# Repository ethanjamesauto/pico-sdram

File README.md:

# pico-sdram

This project attempts to interface a Raspberry Pi Pico with a [32MB SDRAM IC](https://www.winbond.com/resource-files/w9825g6kh_a04.pdf).

## UPDATE - Current State
I have been able to successfully perform single and burst read/writes to the W9825G6KH SDRAM IC. I am running the SDRAM at half the speed of the rp2040 clock - the PIO state machines
are running at the minimum clock divider value.
I don't have full documentation, but some is available in:
* [pico/src/sdram_cmd.c](pico/src/sdram_cmd.c) - contains the main driver code
* [pico/src/pico-sdram.c](pico/src/pico-sdram.c) - example usage of the driver code
* [pico/src/three_74hc595.pio](pico/src/three_74hc595.pio) - PIO driver for the 3x 74hc595 shift registers used to drive the address bus
* [pico/src/data_bus.pio](pico/src/data_bus.pio) - PIO driver for the 16-bit data bus

## Introduction
SDRAM ICs are commonly available in sizes of up to 256MBit (32MB), and most have either an 8-bit or 16-bit data bus width. The control interface uses a total of 23 pins, so there are simply too many pins for an RP2040 to directly drive using GPIOs. 

Shift registers may be reduce the number of GPIOs needed to interface with the ram. Because the RP2040 can only drive shift registers so quickly, the SDRAM chip would need to be driven at a lower clock speed. I propose a solution in which the control pins are driven using shift registers while the data bus is connected directly to the RP2040's GPIOs. This reduces the speed at which commands can be sent to the SDRAM, while still allowing the data bus to run at full speed. This solution has a drawback - it takes more time to send the two commands needed to initiate a read (row activate and read). However, this issue becomes neglible when most reads and writes use large block sizes (for example, when performing 1KB block reads and writes).

## Future Work
Eventually, I'd like to use this SDRAM interface with a PIO-based QSPI interface. The QSPI interface may then appear as a QSPI PSRAM and can be connected to the rp2350's QSPI bus. The pico can then translate "psram" accesses to sdram accesses, which would **allow the pico to natively access sdram in the address space**. This might not be possible.

## Digilent Waveforms SDRAM Protocol Decoder
```js
// rgData: input, raw digital data array
// rgValue: output, decoded data array
// rgFlag: output, decoded flag array

c = rgData.length

for(var i = 0; i < c; i++){
   // take 4 least significant bits
   rgValue[i] = rgData[i] & 0xFF;
   // set flag other than zero for valid data
   rgFlag[i] = 1;
}

// value: value sample
// flag: flag sample
function Value2Text(flag, value) {
  var lower = value & 0xf;
  var addr10 = ((value >> 7) & 1) > 0;
  if (lower & 1) return "";
  if (lower == 14) return "NOP";
  if (lower == 6) return "BURST_TERM";
  if (lower == 10) return addr10 ? "READ_PRECHARGE" : "READ";
  if (lower == 2) return addr10 ? "WRITE_PRECHARGE" : "WRITE";
  if (lower == 12) return "ACTIVATE";
  if (lower == 4) return "PRECHARGE";
  if (lower == 8) return "AUTO_REFRESH";
  if (lower == 0) return "LOAD_MODE";
  return "X";
}
Value2Text(0,0x82)

function Value2Text(flag, value) {
  var lower = value & 0xf;
  var addr10 = ((value >> 7) & 1) > 0;
  if (lower & 1) return "";
  if (lower == 14) return "NOP";
  if (lower == 6) return "BURST_T";
  if (lower == 10) return addr10 ? "READ_P" : "READ";
  if (lower == 2) return addr10 ? "WRITE_P" : "WRITE";
  if (lower == 12) return "ACTIVATE";
  if (lower == 4) return "PRCHG";
  if (lower == 8) return "A_RFRSH";
  if (lower == 0) return "MODE";
  return "X";
}
```

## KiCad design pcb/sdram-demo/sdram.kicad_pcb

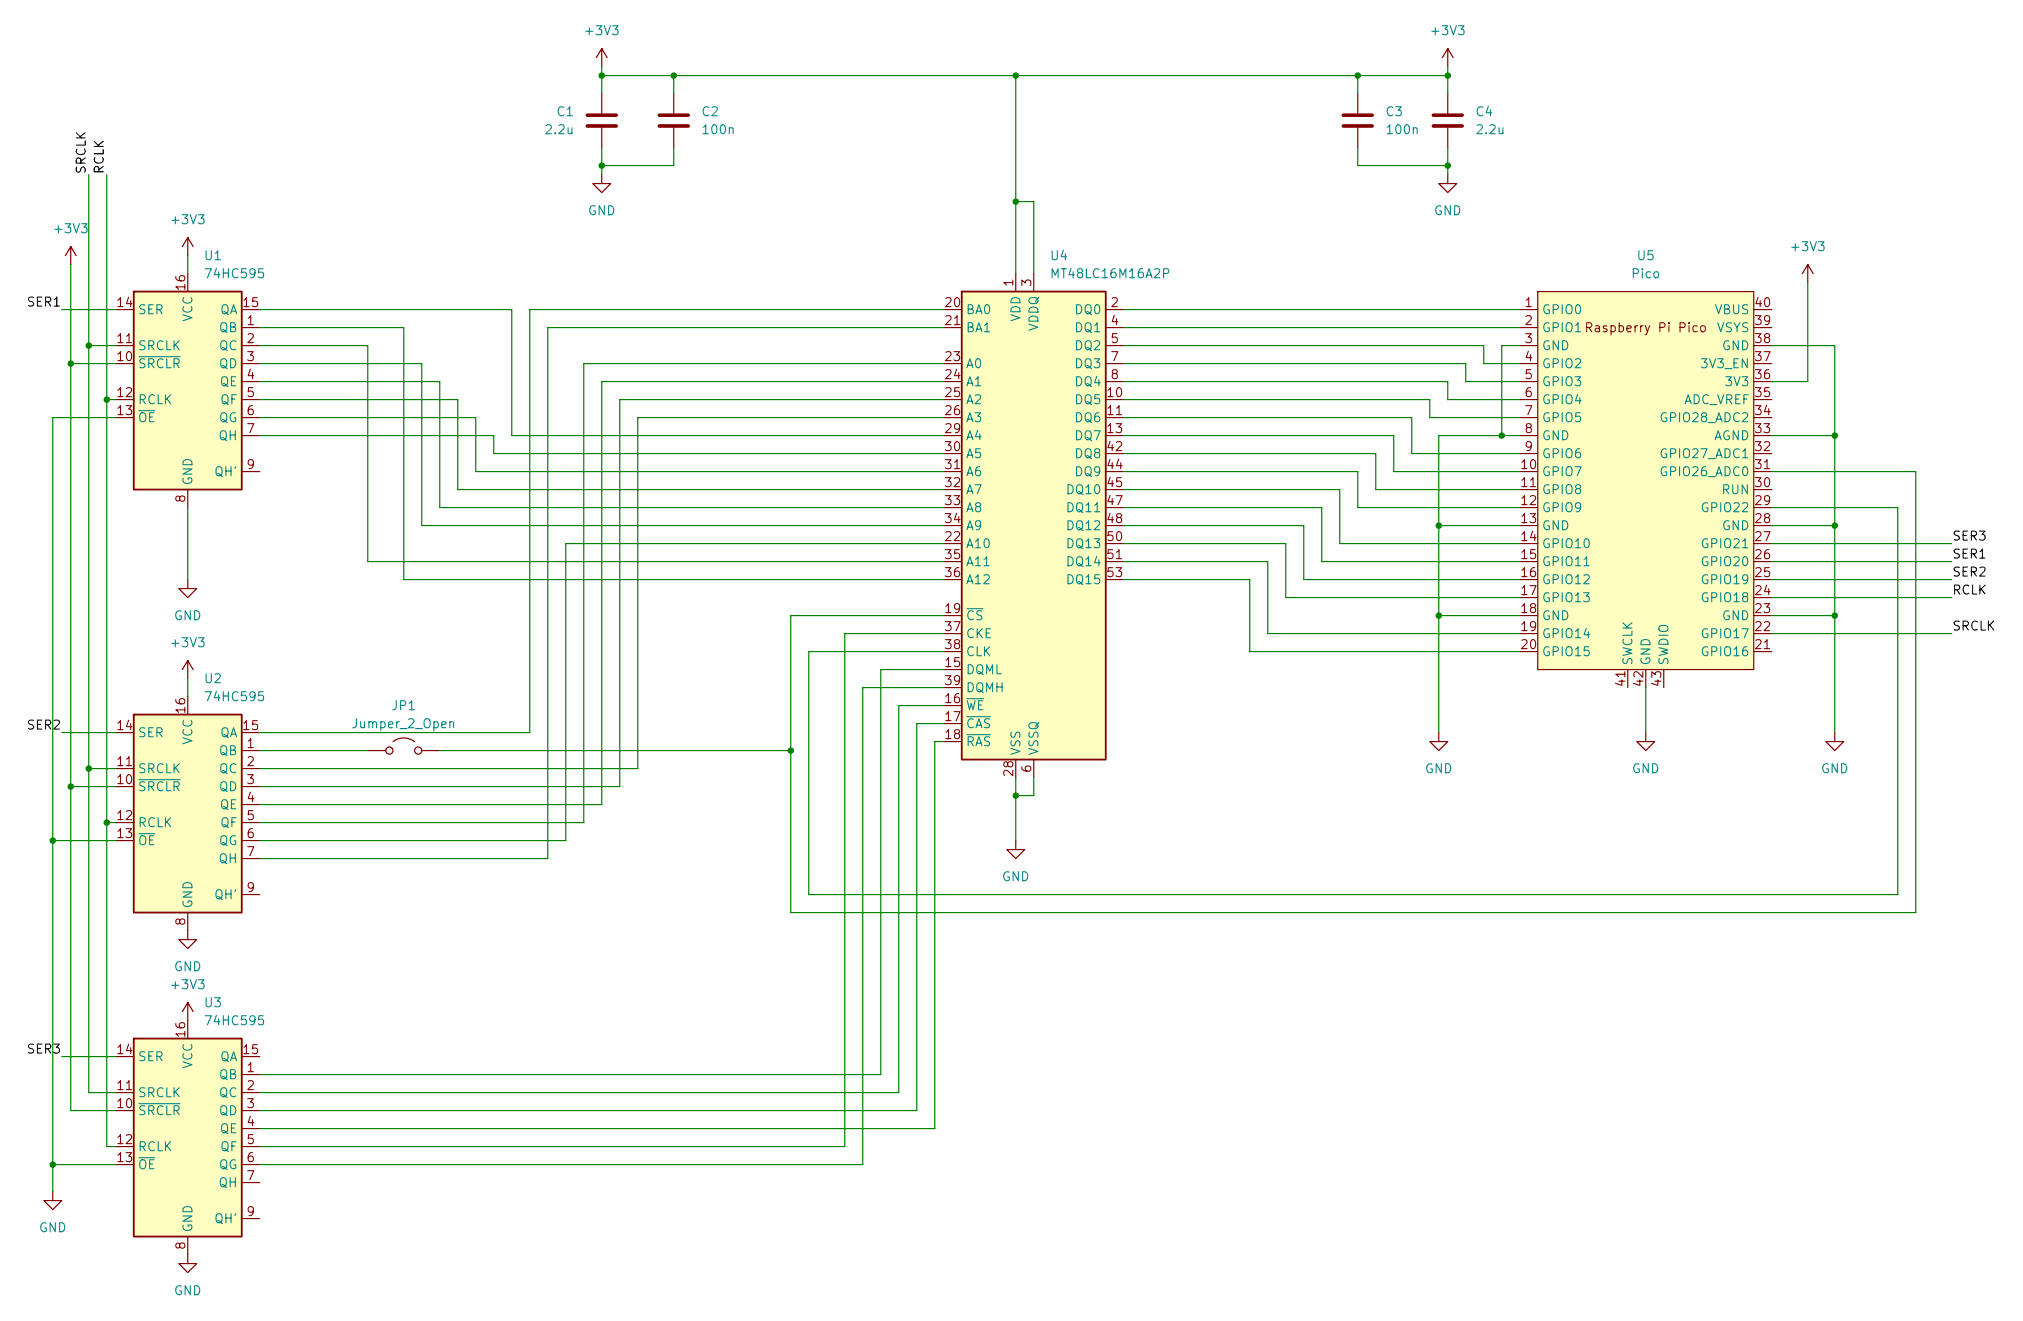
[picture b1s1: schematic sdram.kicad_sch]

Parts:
C1, C4: 2.2u; C_0805_2012Metric_Pad1.18x1.45mm_HandSolder
C2, C3: 100n; C_0805_2012Metric_Pad1.18x1.45mm_HandSolder
JP1: Jumper_2_Open; SolderJumper-2_P1.3mm_Open_Pad1.0x1.5mm
U1, U2, U3: 74HC595; SOIC-16_3.9x9.9mm_P1.27mm
U4: MT48LC16M16A2P; TSOP-II-54_22.2x10.16mm_P0.8mm
U5: Pico; RPi_Pico_SMD_TH

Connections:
+3V3: C1.1, C2.1, C3.1, C4.1, U1.10 (~SRCLR), U1.16 (VCC), U2.10 (~SRCLR), U2.16 (VCC), U3.10 (~SRCLR), U3.16 (VCC), U4.1 (VDD), U4.3 (VDDQ), U4.9 (VDDQ), U4.14 (VDD), U4.27 (VDD), U4.43 (VDDQ), U4.49 (VDDQ), U5.36 (3V3)
/RCLK: U1.12 (RCLK), U2.12 (RCLK), U3.12 (RCLK), U5.24 (GPIO18)
/SER1: U1.14 (SER), U5.26 (GPIO20)
/SER2: U2.14 (SER), U5.25 (GPIO19)
/SER3: U3.14 (SER), U5.27 (GPIO21)
/SRCLK: U1.11 (SRCLK), U2.11 (SRCLK), U3.11 (SRCLK), U5.22 (GPIO17)
GND: C1.2, C2.2, C3.2, C4.2, U1.8 (GND), U1.13 (~OE), U2.8 (GND), U2.13 (~OE), U3.8 (GND), U3.13 (~OE), U4.6 (VSSQ), U4.12 (VSSQ), U4.28 (VSS), U4.41 (VSS), U4.46 (VSSQ), U4.52 (VSSQ), U4.54 (VSS), U5.3 (GND), U5.8 (GND), U5.13 (GND), U5.18 (GND), U5.23 (GND), U5.28 (GND), U5.33 (AGND), U5.38 (GND), U5.42 (GND)
unnamed: JP1.1 (A), U2.1 (QB)
unnamed: JP1.2 (B), U4.19 (~CS), U5.31 (GPIO26_ADC0)
unnamed: U1.15 (QA), U4.29 (A4)
unnamed: U1.1 (QB), U4.36 (A12)
unnamed: U1.2 (QC), U4.35 (A11)
unnamed: U1.3 (QD), U4.34 (A9)
unnamed: U1.4 (QE), U4.33 (A8)
unnamed: U1.5 (QF), U4.32 (A7)
unnamed: U1.6 (QG), U4.31 (A6)
unnamed: U1.7 (QH), U4.30 (A5)
unnamed: U2.15 (QA), U4.20 (BA0)
unnamed: U2.2 (QC), U4.26 (A3)
unnamed: U2.3 (QD), U4.25 (A2)
unnamed: U2.4 (QE), U4.24 (A1)
unnamed: U2.5 (QF), U4.23 (A0)
unnamed: U2.6 (QG), U4.22 (A10)
unnamed: U2.7 (QH), U4.21 (BA1)
unnamed: U3.1 (QB), U4.15 (DQML)
unnamed: U3.2 (QC), U4.16 (~WE)
unnamed: U3.3 (QD), U4.17 (~CAS)
unnamed: U3.4 (QE), U4.18 (~RAS)
unnamed: U3.5 (QF), U4.37 (CKE)
unnamed: U3.6 (QG), U4.39 (DQMH)
unnamed: U4.38 (CLK), U5.29 (GPIO22)
unnamed: U4.2 (DQ0), U5.1 (GPIO0)
unnamed: U4.4 (DQ1), U5.2 (GPIO1)
unnamed: U4.5 (DQ2), U5.4 (GPIO2)
unnamed: U4.7 (DQ3), U5.5 (GPIO3)
unnamed: U4.8 (DQ4), U5.6 (GPIO4)
unnamed: U4.10 (DQ5), U5.7 (GPIO5)
unnamed: U4.11 (DQ6), U5.9 (GPIO6)
unnamed: U4.13 (DQ7), U5.10 (GPIO7)
unnamed: U4.42 (DQ8), U5.11 (GPIO8)
unnamed: U4.44 (DQ9), U5.12 (GPIO9)
unnamed: U4.45 (DQ10), U5.14 (GPIO10)
unnamed: U4.47 (DQ11), U5.15 (GPIO11)
unnamed: U4.48 (DQ12), U5.16 (GPIO12)
unnamed: U4.50 (DQ13), U5.17 (GPIO13)
unnamed: U4.51 (DQ14), U5.19 (GPIO14)
unnamed: U4.53 (DQ15), U5.20 (GPIO15)

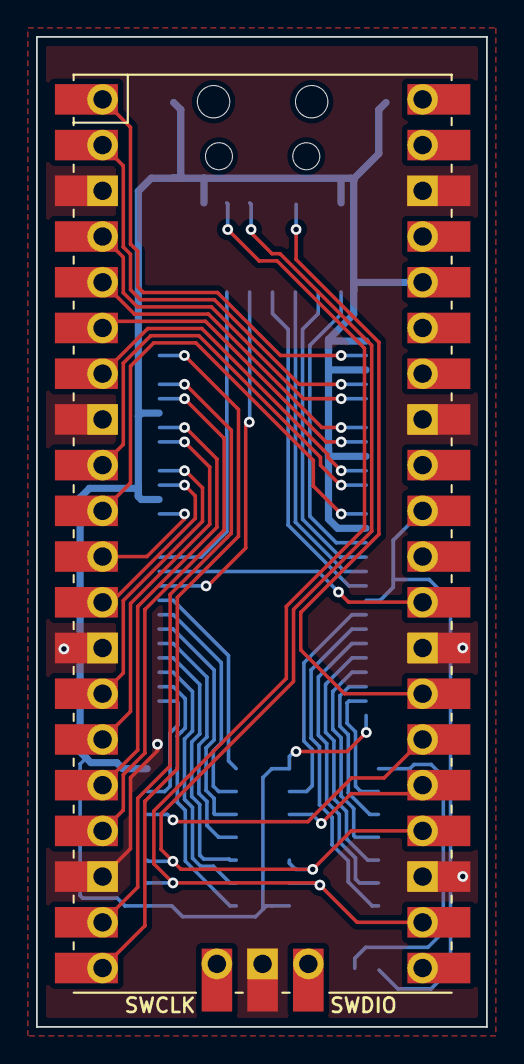
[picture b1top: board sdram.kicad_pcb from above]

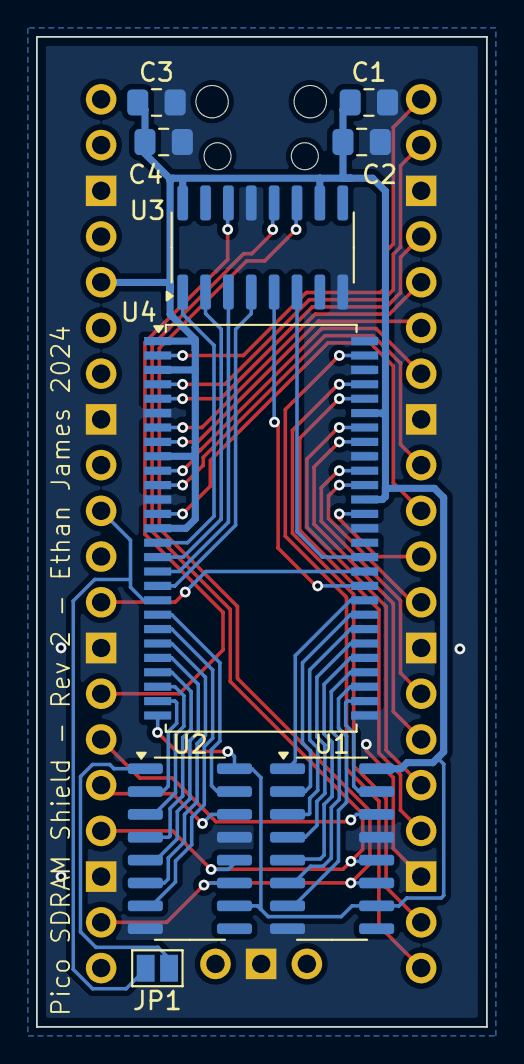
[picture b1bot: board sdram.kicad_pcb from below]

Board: 2 copper layers, 25.0 x 55.0 mm, 10 parts (9 on the bottom side), 47 nets.

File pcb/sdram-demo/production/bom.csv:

Designator,Footprint,Quantity,Value,LCSC Part #
"C1, C4",0805,2,2.2u,
"C2, C3",0805,2,100n,
JP1,SolderJumper-2_P1.3mm_Open_Pad1.0x1.5mm,1,Jumper_2_Open,
"U1, U2, U3",SOIC-16_3.9x9.9mm_P1.27mm,3,74HC595,
U4,TSOP-II-54_22.2x10.16mm_P0.8mm,1,MT48LC16M16A2P,
U5,RPi_Pico_SMD_TH,1,Pico,

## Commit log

2024-11-23 Add PCB
2024-11-23 Add images
2024-11-23 Update pcb
2024-11-23 Update pcb and add pio code
2024-11-23 Update pio program
2024-11-23 add sdram submodule
2024-11-24 Add pico software
2024-11-24 Update comment
2024-11-25 add data bus pio driver
2024-11-25 Add comments
2024-11-25 Use gpio to sync PIOs
2024-11-25 replace gpio sync with a simpler method (enabling both sms at exactly the same time)
2024-11-25 Add sdram clock
2024-11-26 Add separate clkgen sm
2024-11-26 get clkgen sync working, add some config headers
2024-11-26 add note about phase sync
2024-11-26 Add temporary fix to sync clk phase
2024-11-26 Add some sdram commands
2024-11-26 Add write cmd demo
2024-11-26 fix clock polarity
2024-11-26 change to a better way of resyncing pios
2024-11-26 wip make data take up less space in memory
2024-11-26 reorganize code
2024-11-27 Add code to auto-refresh entire memory
2024-11-27 wip - half time the shift register sm
2024-11-27 wip - add attempt at shift register sm that does not lose sync when fifo empty
2024-11-27 Add two tests
2024-11-28 Add HAL code for setting mode register
2024-11-28 comment
2024-11-28 remove old file
2024-11-28 remove old file 2/2
2024-11-28 Change pinout
2024-11-28 change demo a bit
2024-11-28 Add power-up seqeunce
2024-11-28 Clean up code
2024-11-30 Add write function
2024-11-30 Finish adding write cmd
2024-11-30 Add some of read command
2024-11-30 Add wait command
2024-11-30 Update demo
2024-11-30 wip - adding input mode on data bus
2024-11-30 update bus mode func
2024-11-30 add read1 function
2024-11-30 Add cmds spreadsheet
2024-12-01 introduce new bugs
2024-12-01 move problems out of sight
2024-12-01 add pinout from rev1 pcb
2024-12-14 Add verilog sim
2024-12-14 reorganize pinout data
2024-12-14 remove code that sets pins to output to avoid data contention
2024-12-14 simplify demo
2024-12-14 wip - adding input pullups so that data can be seen when sdram controls bus
2024-12-14 add rp2040 target
2024-12-14 Update sim files
2024-12-14 Update simulation files
2024-12-15 Fix read happening at wrong time for cas latency 3
2024-12-15 add full memory test
2024-12-22 Fix silly linker errors
2024-12-23 Update clkdiv settings
2024-12-23 Add WIP burst read functions
2024-12-23 Add template for future sdram controller
2024-12-23 Update testbench
2024-12-23 Add rev2 PCB
2024-12-23 Add zip for rev2
2024-12-24 wip - add full page read function
2025-01-02 Add support for rev 2 board
2025-01-02 Add burst 8 test
2025-01-02 Add debug interface
2025-01-07 working cmd/data demo here
2025-01-07 Add high speed demo
2025-01-07 Add process cmd function
2025-01-08 integrate new code with old code - read write demo
2025-01-08 Fix some issues
2025-01-08 Switch to rev2 layout
2025-01-08 working demo
2025-01-08 Add memtest demo with burst 8 reads
2025-01-08 Memtest now tests all banks
2025-01-08 Somehow got it working at the full clock speed
2025-01-08 Memtest now prints out total # of successes and failures
2025-01-08 Add code to configure data bus number of transactions
2025-01-09 Remove old functions
2025-01-09 Update sim
2025-01-09 Add .gitignore
2025-01-09 Add Debug mode - lower clock speed and repeated single read/write
2025-01-09 Fix sdram_exec bug that disallowed data lengths longer than cmd lengths
2025-01-09 Add write8 function
2025-01-09 Change sdram_exec functions a bit and add test with burst writes and reads
2025-01-09 Test full page burst mode
2025-01-09 Add some code for dma full page reads
2025-01-09 Change burst demo to 32
2025-01-09 Add dma for cmd channel
2025-01-09 Full page burst reads!!!!
2025-01-10 Add page writes with DMA
2025-01-10 Clean up and refactor code
2025-01-10 Remove old code
2025-01-10 Update sim for v2
2025-01-10 Rework sm start logic a bit
2025-01-10 Remove need for resyncing cmd sm with clock
2025-01-10 Add warning comment
2025-01-12 Add vga stuff
2025-01-12 Add stuff
2025-01-12 more stuf
2025-01-13 Add filling sdram from serial
2025-01-13 Add bank interleaved full page reads for nonstop data output (stackoverflow said it couldn't be done)
2025-01-13 Make input faster
2025-01-13 Add test notebook
2025-01-13 Add endless dma
2025-01-13 make picture look better by adding delays to hsync and vsync
2025-01-14 fix timing
2025-01-14 simplify code
2025-01-14 waste less ram
2025-01-14 Add multiple frames
2025-01-15 fix issue
2025-01-16 add refresh code
2025-04-09 Get rid of some warnings
2025-04-09 Add comments and remove old code
